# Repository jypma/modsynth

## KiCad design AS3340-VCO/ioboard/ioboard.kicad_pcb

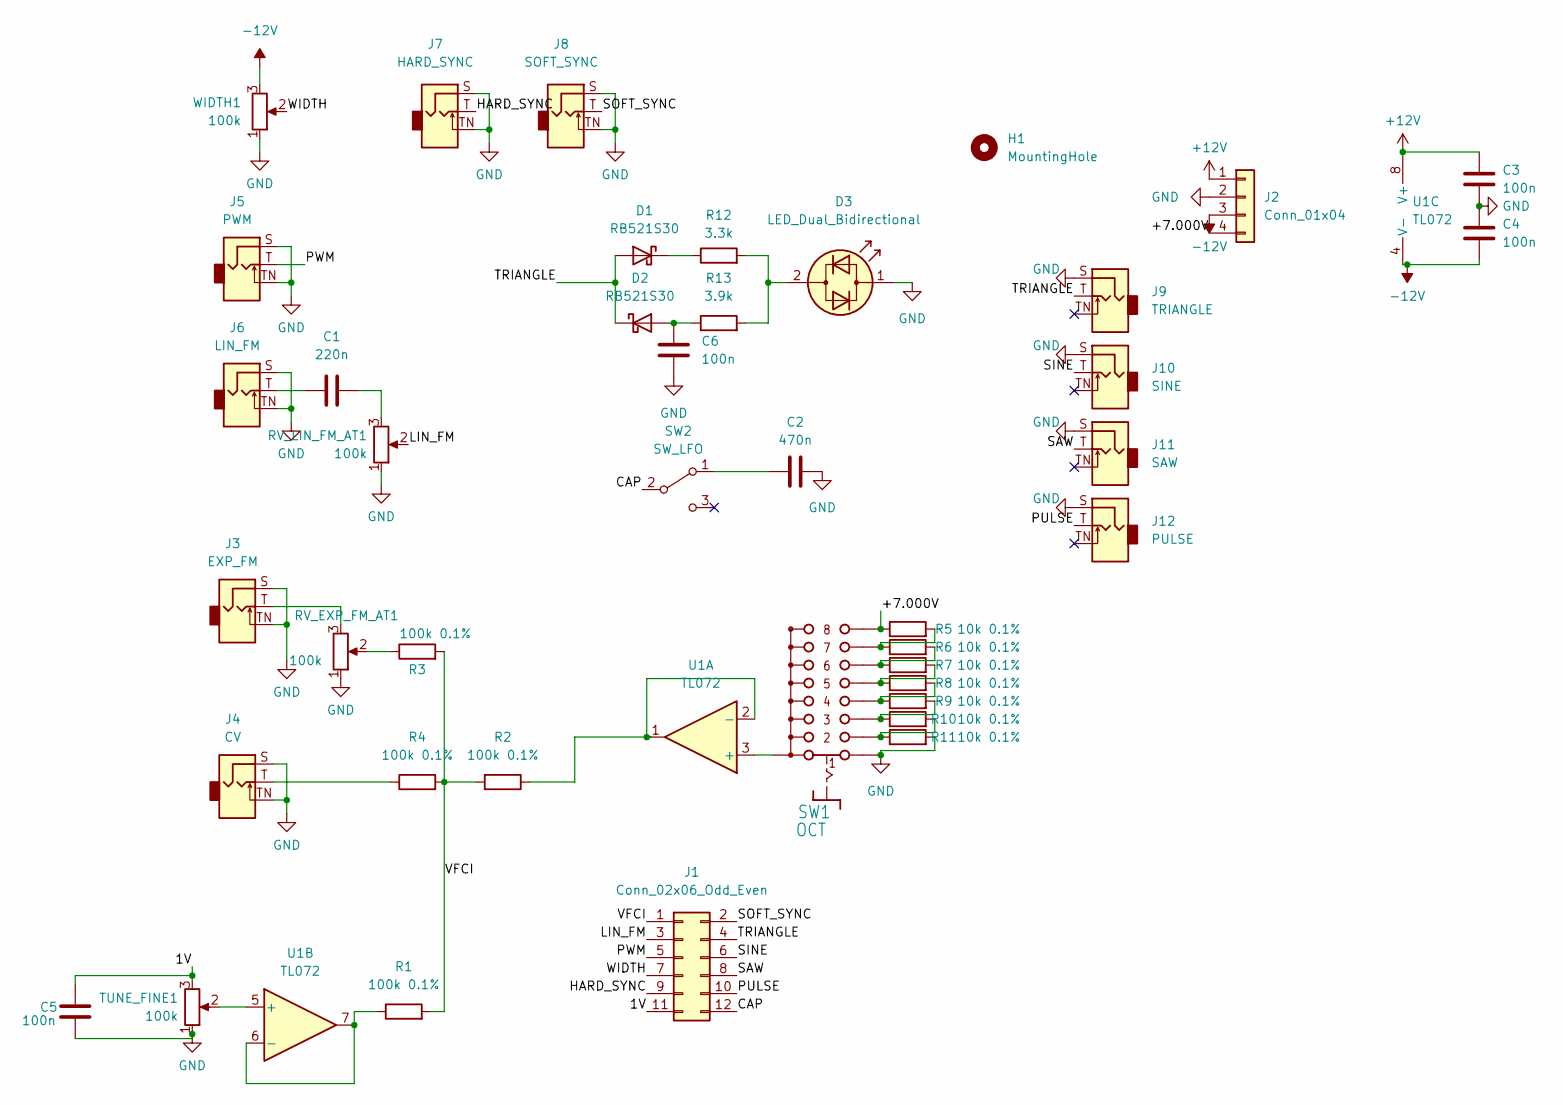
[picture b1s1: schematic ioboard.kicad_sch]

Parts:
C1: 220n; C_0603_1608Metric_Pad1.08x0.95mm_HandSolder
C2: 470n; C_Rect_L7.0mm_W3.5mm_P5.00mm
C3, C4, C5, C6: 100n; C_0603_1608Metric_Pad1.08x0.95mm_HandSolder
D1, D2: RB521S30; D_SOD-523
D3: LED_Dual_Bidirectional; LED_D3.0mm
H1: MountingHole; MountingHole_3.2mm_M3_NoCourt
J1: Conn_02x06_Odd_Even; PinHeader_2x06_P2.54mm_Vertical
J2: Conn_01x04; PinHeader_1x04_P2.54mm_Vertical
J3: EXP_FM; Jack_3.5mm_QingPu_WQP-PJ398SM_Vertical_CircularHoles
J4: CV; Jack_3.5mm_QingPu_WQP-PJ398SM_Vertical_CircularHoles
J5: PWM; Jack_3.5mm_QingPu_WQP-PJ398SM_Vertical_CircularHoles
J6: LIN_FM; Jack_3.5mm_QingPu_WQP-PJ398SM_Vertical_CircularHoles
J7: HARD_SYNC; Jack_3.5mm_QingPu_WQP-PJ398SM_Vertical_CircularHoles
J8: SOFT_SYNC; Jack_3.5mm_QingPu_WQP-PJ398SM_Vertical_CircularHoles
J9: TRIANGLE; Jack_3.5mm_QingPu_WQP-PJ398SM_Vertical_CircularHoles
J10: SINE; Jack_3.5mm_QingPu_WQP-PJ398SM_Vertical_CircularHoles
J11: SAW; Jack_3.5mm_QingPu_WQP-PJ398SM_Vertical_CircularHoles
J12: PULSE; Jack_3.5mm_QingPu_WQP-PJ398SM_Vertical_CircularHoles
R1, R2, R3, R4: 100k 0.1%; R_0603_1608Metric_Pad0.98x0.95mm_HandSolder
R5, R6, R7, R8, R9, R10, R11: 10k 0.1%; R_0603_1608Metric_Pad0.98x0.95mm_HandSolder
R12: 3.3k; R_0603_1608Metric_Pad0.98x0.95mm_HandSolder
R13: 3.9k; R_0603_1608Metric_Pad0.98x0.95mm_HandSolder
RV_EXP_FM_AT1: 100k; Potentiometer_Alps_RK09K_Single_Vertical
RV_LIN_FM_AT1: 100k; Potentiometer_Alps_RK09K_Single_Vertical
SW1: OCT; Rotary-Switch-8-ALPS-SRBV
SW2: SW_LFO; SW_Toggle_Blue_wSlots
TUNE_FINE1: 100k; Potentiometer_Alps_RK09K_Single_Vertical
U1: TL072; SOIC-8_3.9x4.9mm_P1.27mm
WIDTH1: 100k; Potentiometer_Alps_RK09K_Single_Vertical

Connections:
+12V: C3.1, J2.1, U1.8 (V+)
-12V: C4.2, J2.3, U1.4 (V-), WIDTH1.3
/1V: C5.1, J1.11, TUNE_FINE1.3
/+7.000V: J2.4, R5.1, SW1.H (8)
/CAP: J1.12, SW2.2 (B)
/HARD_SYNC: J1.9, J7.T
/LIN_FM: J1.3, RV_LIN_FM_AT1.2
/PULSE: J1.10, J12.T
/PWM: J1.5, J5.T
/SAW: J1.8, J11.T
/SINE: J1.6, J10.T
/SOFT_SYNC: J1.2, J8.T
/TRIANGLE: D1.2 (A), D2.1 (K), J1.4, J9.T
/VFCI: J1.1, R1.2, R2.2, R3.2, R4.2
/WIDTH: J1.7, WIDTH1.2
GND: C2.2, C3.2, C4.1, C5.2, C6.2, D3.1 (KA), J2.2, J3.S, J3.TN, J4.S, J4.TN, J5.S, J5.TN, J6.S, J6.TN, J7.S, J7.TN, J8.S, J8.TN, J9.S, J10.S, J11.S, J12.S, R11.2, RV_EXP_FM_AT1.1, RV_LIN_FM_AT1.1, SW1.A (1), TUNE_FINE1.1, WIDTH1.1
unnamed: C1.1, J6.T
unnamed: C1.2, RV_LIN_FM_AT1.3
unnamed: C2.1, SW2.1 (A)
unnamed: C6.1, D2.2 (A), R13.1
unnamed: D1.1 (K), R12.1
unnamed: D3.2 (AK), R12.2, R13.2
unnamed: J3.T, RV_EXP_FM_AT1.3
unnamed: J4.T, R4.1
unnamed: R1.1, U1.6 (-), U1.7
unnamed: R2.1, U1.1, U1.2 (-)
unnamed: R3.1, RV_EXP_FM_AT1.2
unnamed: R5.2, R6.1, SW1.G (7)
unnamed: R6.2, R7.1, SW1.F (6)
unnamed: R7.2, R8.1, SW1.E (5)
unnamed: R8.2, R9.1, SW1.D (4)
unnamed: R9.2, R10.1, SW1.C (3)
unnamed: R10.2, R11.1, SW1.B (2)
unnamed: SW1.COM (A), SW1.COM2 (A), U1.3 (+)
unnamed: TUNE_FINE1.2, U1.5 (+)

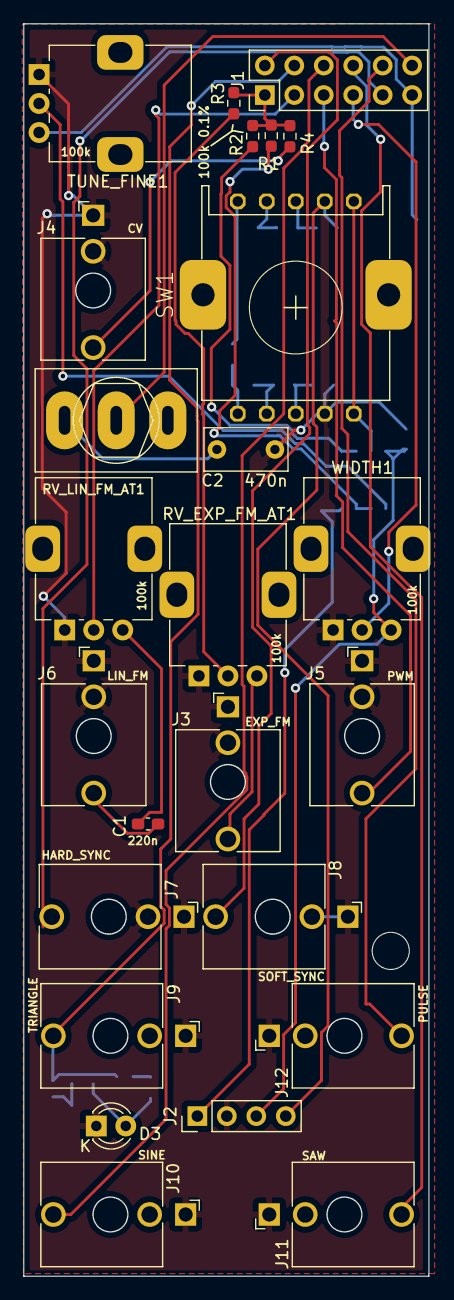
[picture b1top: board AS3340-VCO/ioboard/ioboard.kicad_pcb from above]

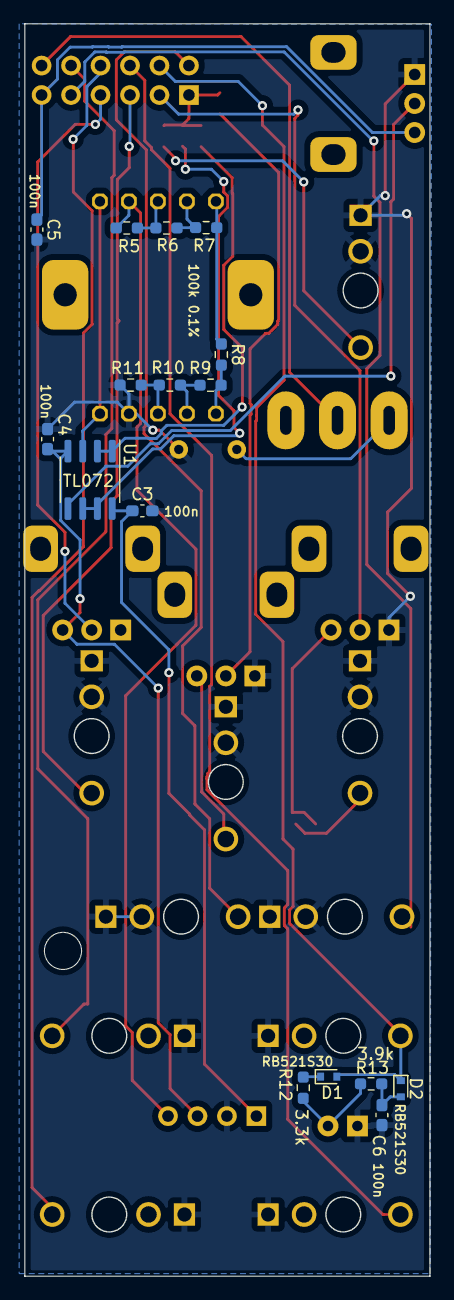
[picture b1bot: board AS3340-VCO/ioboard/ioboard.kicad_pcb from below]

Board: 2 copper layers, 34.9 x 108.0 mm, 42 parts (16 on the bottom side), 35 nets.

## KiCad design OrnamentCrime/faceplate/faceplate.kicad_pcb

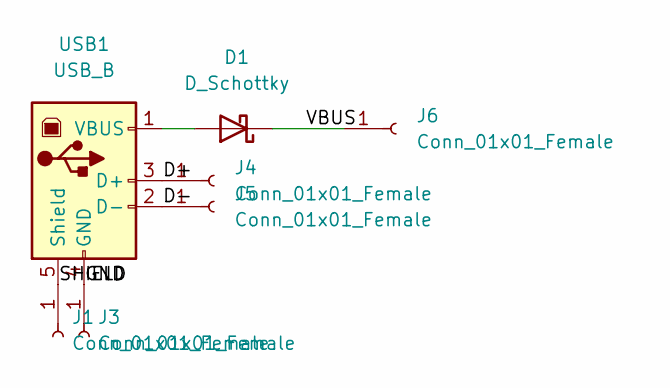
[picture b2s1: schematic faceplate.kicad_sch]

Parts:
D1: D_Schottky; D_SMB_Handsoldering
J1, J3, J4, J5, J6: Conn_01x01_Female; TestPoint_Pad_3.0x3.0mm
USB1: USB_B; USB_B_TE_5787834_Vertical

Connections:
/D+: J4.1, USB1.3 (D+)
/D-: J5.1, USB1.2 (D-)
/GND: J3.1, USB1.4 (GND)
/SHIELD: J1.1, USB1.5 (Shield)
/VBUS: D1.1 (K), J6.1
unnamed: D1.2 (A), USB1.1 (VBUS)

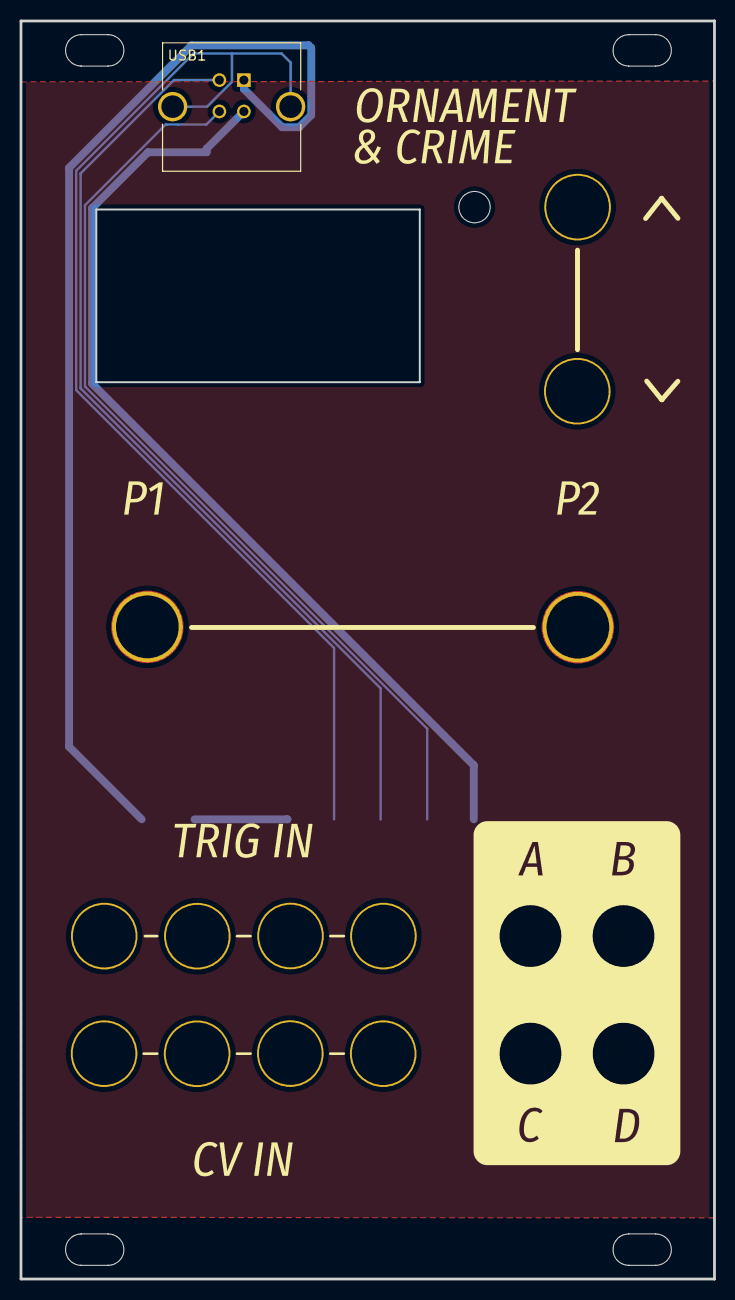
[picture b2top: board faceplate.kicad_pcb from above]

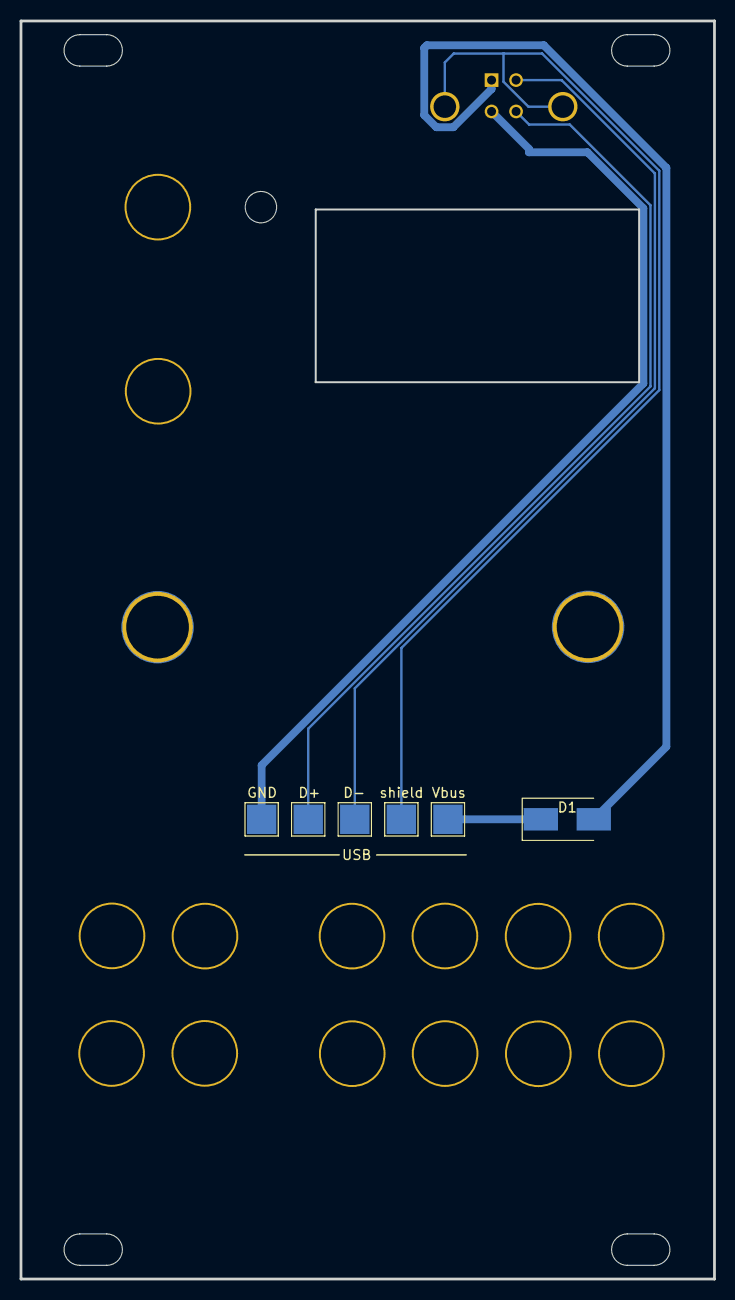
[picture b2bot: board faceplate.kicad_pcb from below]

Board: 2 copper layers, 70.8 x 128.4 mm, 9 parts (6 on the bottom side), 6 nets.

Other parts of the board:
GND: MountingHole_7.2mm_Pad_TopBottom
GND#2: MountingHole_7.2mm_Pad_TopBottom

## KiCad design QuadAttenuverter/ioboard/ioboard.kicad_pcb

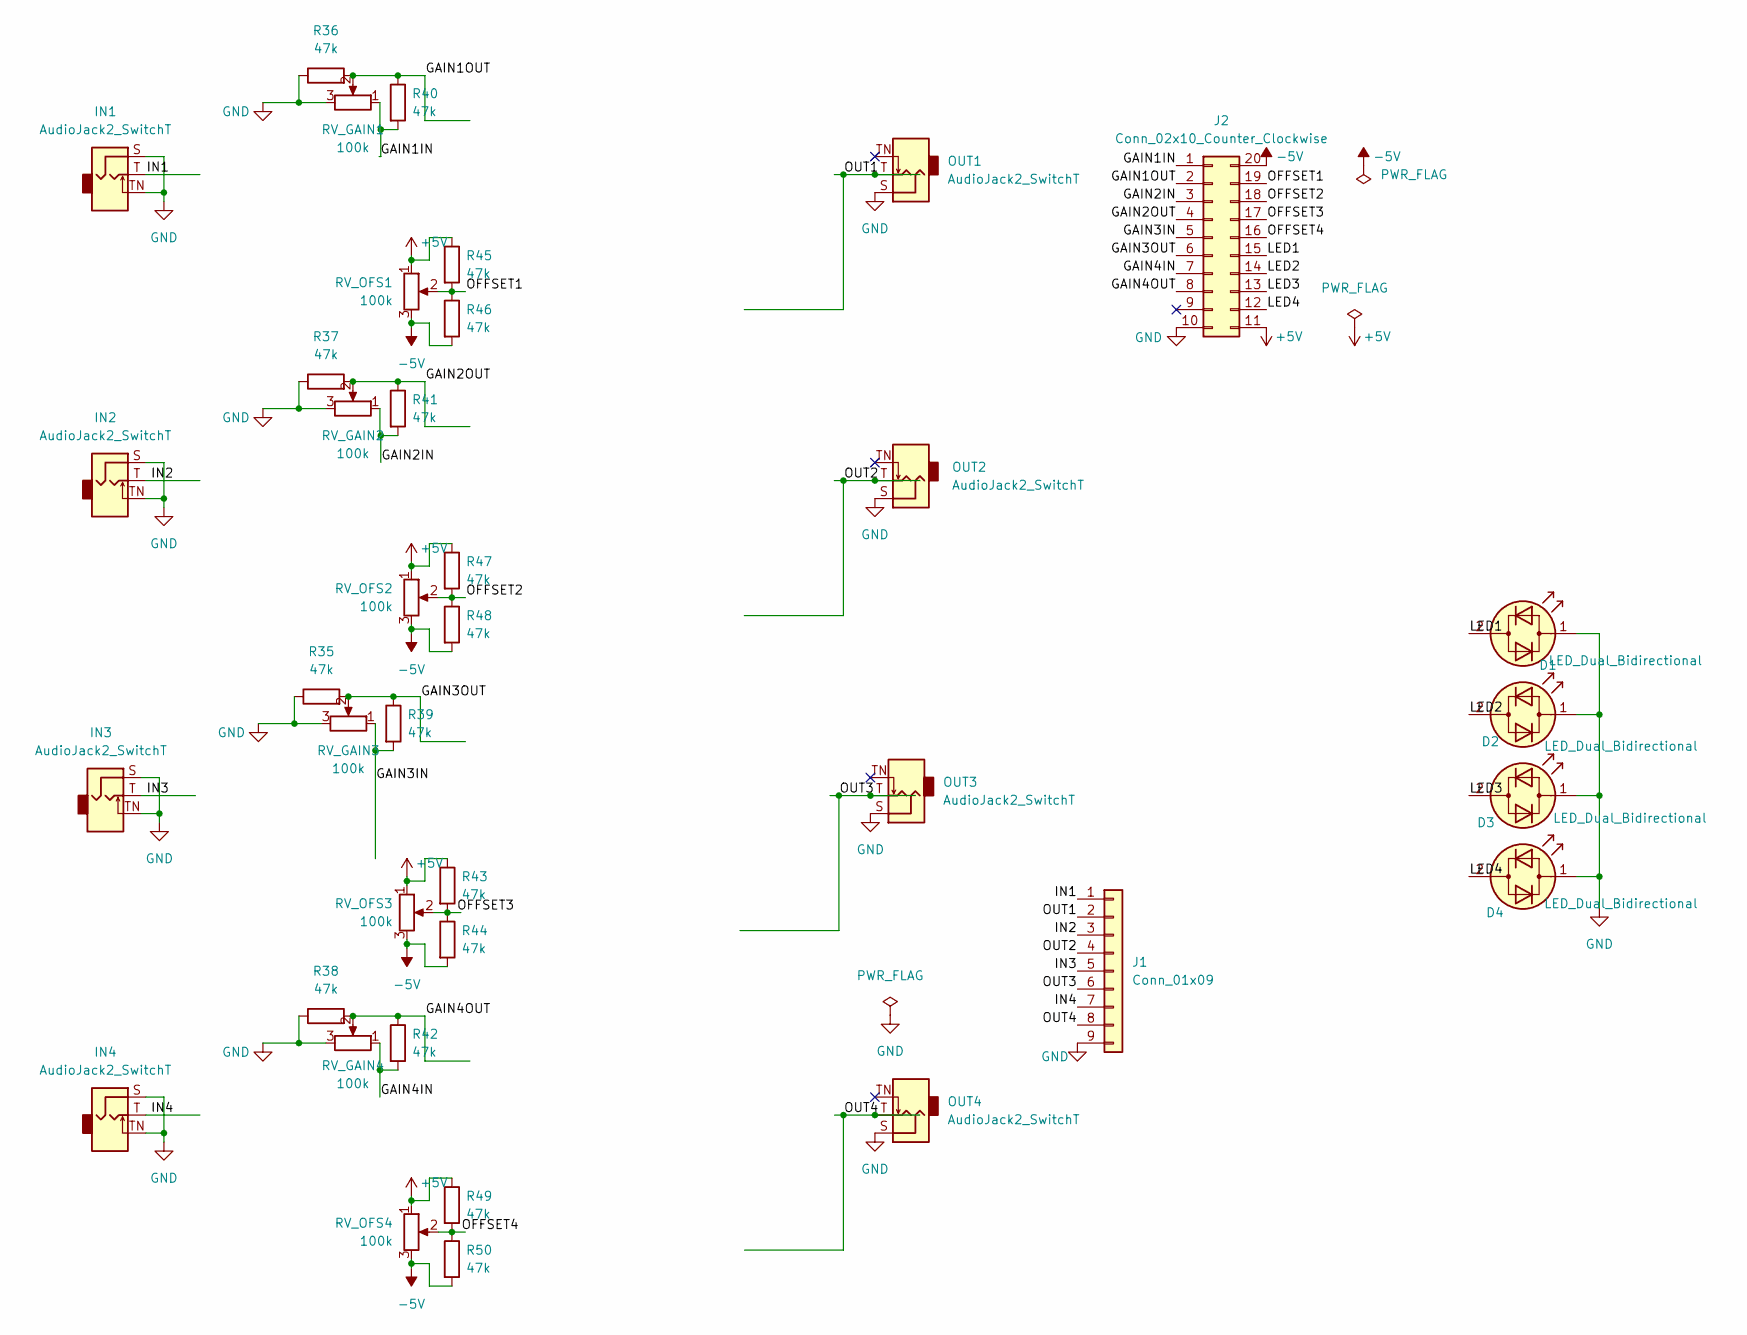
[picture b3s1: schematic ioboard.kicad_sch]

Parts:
D1, D2, D3, D4: LED_Dual_Bidirectional; LED_D3.0mm
IN1, IN2, IN3, IN4: AudioJack2_SwitchT; Jack_3.5mm_QingPu_WQP-PJ398SM_Vertical_CircularHoles
J1: Conn_01x09; PinHeader_1x09_P2.54mm_Vertical
J2: Conn_02x10_Counter_Clockwise; PinHeader_2x10_P2.54mm_Vertical
OUT1, OUT2, OUT3, OUT4: AudioJack2_SwitchT; Jack_3.5mm_QingPu_WQP-PJ398SM_Vertical_CircularHoles
R35, R36, R37, R38, R39, R40, R41, R42, R43, R44, R45, R46, R47, R48, R49, R50: 47k; R_0603_1608Metric_Pad0.98x0.95mm_HandSolder
RV_GAIN1, RV_GAIN2, RV_GAIN3, RV_GAIN4: 100k; Potentiometer_Alps_RK09K_Single_Vertical
RV_OFS1, RV_OFS2, RV_OFS3, RV_OFS4: 100k; Potentiometer_Alps_RK09K_Single_Vertical

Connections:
+5V: J2.11, R43.1, R45.1, R47.1, R49.1, RV_OFS1.1, RV_OFS2.1, RV_OFS3.1, RV_OFS4.1
-5V: J2.20, R44.2, R46.2, R48.2, R50.2, RV_OFS1.3, RV_OFS2.3, RV_OFS3.3, RV_OFS4.3
/GAIN1IN: J2.1, R40.2, RV_GAIN1.1
/GAIN1OUT: J2.2, R36.2, R40.1, RV_GAIN1.2
/GAIN2IN: J2.3, R41.2, RV_GAIN2.1
/GAIN2OUT: J2.4, R37.2, R41.1, RV_GAIN2.2
/GAIN3IN: J2.5, R39.2, RV_GAIN3.1
/GAIN3OUT: J2.6, R35.2, R39.1, RV_GAIN3.2
/GAIN4IN: J2.7, R42.2, RV_GAIN4.1
/GAIN4OUT: J2.8, R38.2, R42.1, RV_GAIN4.2
/IN1: IN1.T, J1.1
/IN2: IN2.T, J1.3
/IN3: IN3.T, J1.5
/IN4: IN4.T, J1.7
/LED1: D1.2 (AK), J2.15
/LED2: D2.2 (AK), J2.14
/LED3: D3.2 (AK), J2.13
/LED4: D4.2 (AK), J2.12
/OFFSET1: J2.19, R45.2, R46.1, RV_OFS1.2
/OFFSET2: J2.18, R47.2, R48.1, RV_OFS2.2
/OFFSET3: J2.17, R43.2, R44.1, RV_OFS3.2
/OFFSET4: J2.16, R49.2, R50.1, RV_OFS4.2
/OUT1: J1.2, OUT1.T
/OUT2: J1.4, OUT2.T
/OUT3: J1.6, OUT3.T
/OUT4: J1.8, OUT4.T
GND: D1.1 (KA), D2.1 (KA), D3.1 (KA), D4.1 (KA), IN1.S, IN1.TN, IN2.S, IN2.TN, IN3.S, IN3.TN, IN4.S, IN4.TN, J1.9, J2.10, OUT1.S, OUT2.S, OUT3.S, OUT4.S, R35.1, R36.1, R37.1, R38.1, RV_GAIN1.3, RV_GAIN2.3, RV_GAIN3.3, RV_GAIN4.3

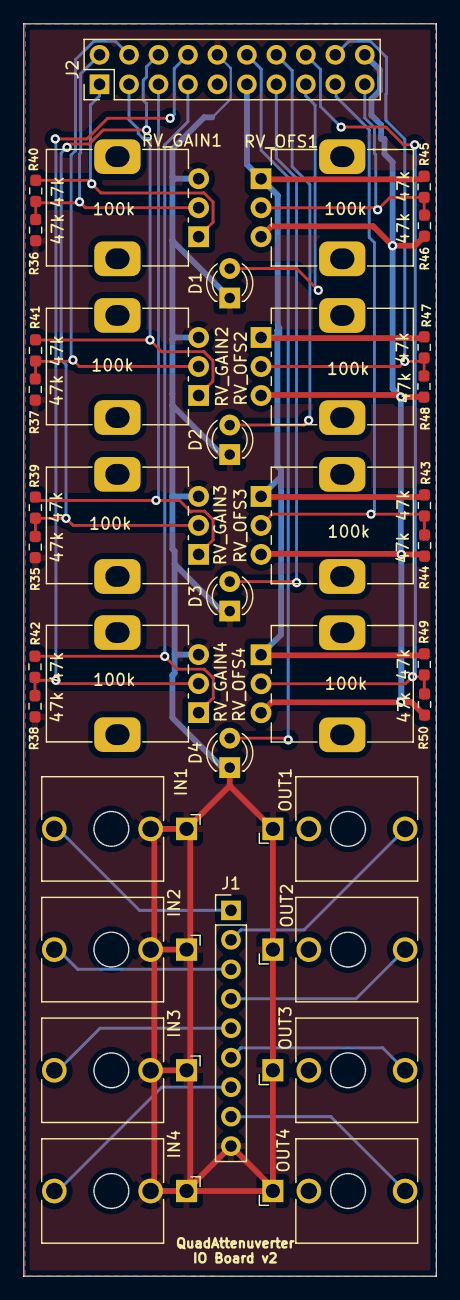
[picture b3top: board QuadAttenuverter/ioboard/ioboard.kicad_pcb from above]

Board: 2 copper layers, 35.6 x 108.0 mm, 38 parts (0 on the bottom side), 27 nets.
